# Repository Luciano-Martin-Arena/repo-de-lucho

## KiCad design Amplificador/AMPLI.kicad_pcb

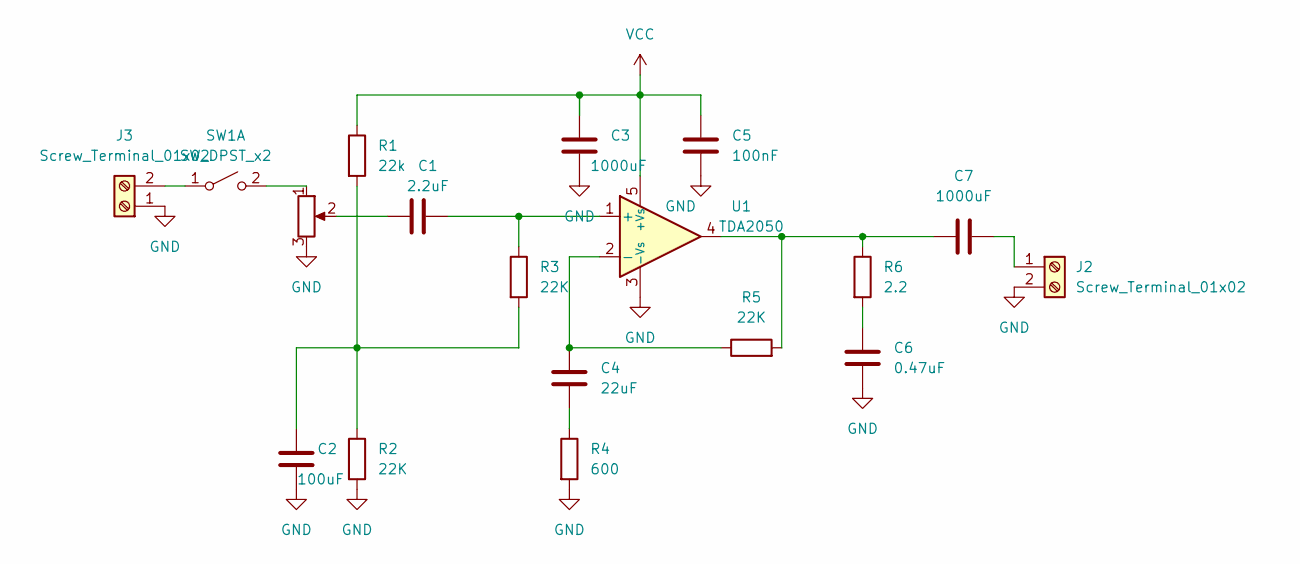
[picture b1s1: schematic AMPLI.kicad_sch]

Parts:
C1: 2.2uF; C_Disc_D3.0mm_W1.6mm_P2.50mm
C2: 100uF; C_Disc_D3.0mm_W1.6mm_P2.50mm
C3, C7: 1000uF; C_Disc_D3.0mm_W1.6mm_P2.50mm
C4: 22uF; C_Disc_D3.0mm_W1.6mm_P2.50mm
C5: 100nF; C_Disc_D3.0mm_W1.6mm_P2.50mm
C6: 0.47uF; C_Disc_D3.0mm_W1.6mm_P2.50mm
J2, J3: Screw_Terminal_01x02; BORNERA2_AZUL
R1: 22k; R_Axial_DIN0204_L3.6mm_D1.6mm_P7.62mm_Horizontal
R2, R3, R5: 22K; R_Axial_DIN0204_L3.6mm_D1.6mm_P7.62mm_Horizontal
R4: 600; R_Axial_DIN0204_L3.6mm_D1.6mm_P7.62mm_Horizontal
R6: 2.2; R_Axial_DIN0204_L3.6mm_D1.6mm_P7.62mm_Horizontal
RV1: R_Potentiometer; Potentiometer_Piher_PC-16_Single_Horizontal
SW1: SW_DPST_x2; PinHeader_1x03_P2.54mm_Vertical
U1: TDA2050; TO-220-5_P3.4x3.7mm_StaggerOdd_Lead3.8mm_Vertical

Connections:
GND: C2.2, C3.2, C5.2, C6.2, J2.2, J3.1, R2.2, R4.2, RV1.3, U1.3 (-Vs)
unnamed: C1.1, RV1.2
unnamed: C2.1, R1.2, R2.1, R3.2
unnamed: C4.2, R4.1
unnamed: C6.1, R6.2
unnamed: C7.1, R5.2, R6.1, U1.4
unnamed: C7.2, J2.1
unnamed: J3.2, SW1.1 (A)
unnamed: RV1.1, SW1.2 (B)
unnamed: C1.2, R3.1, U1.1 (+)
unnamed: C4.1, R5.1, U1.2 (-)
VCC: C3.1, C5.1, R1.1, U1.5 (+Vs)

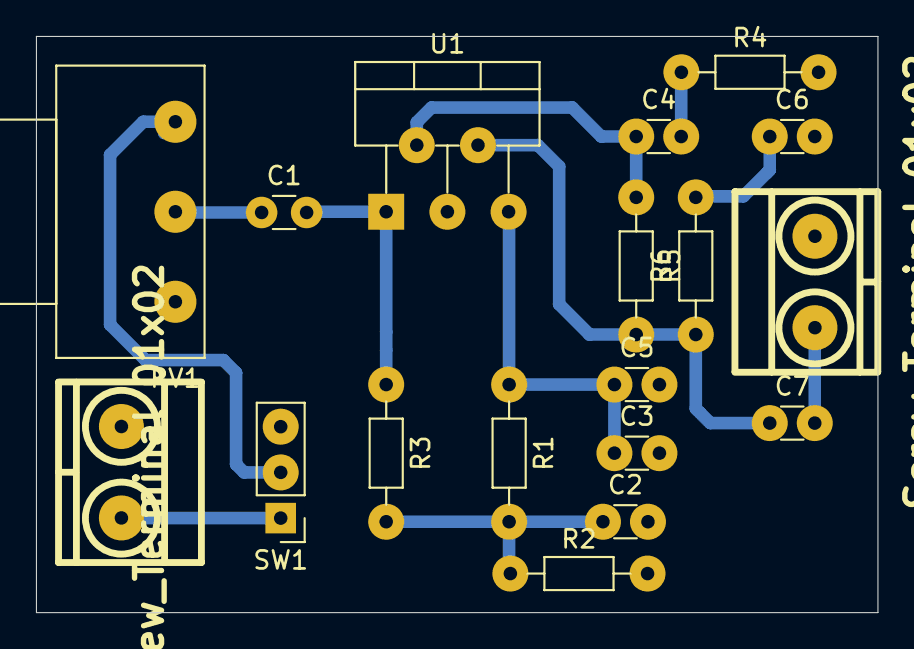
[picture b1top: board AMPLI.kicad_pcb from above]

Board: 2 copper layers, 46.8 x 32.0 mm, 18 parts (0 on the bottom side), 12 nets.

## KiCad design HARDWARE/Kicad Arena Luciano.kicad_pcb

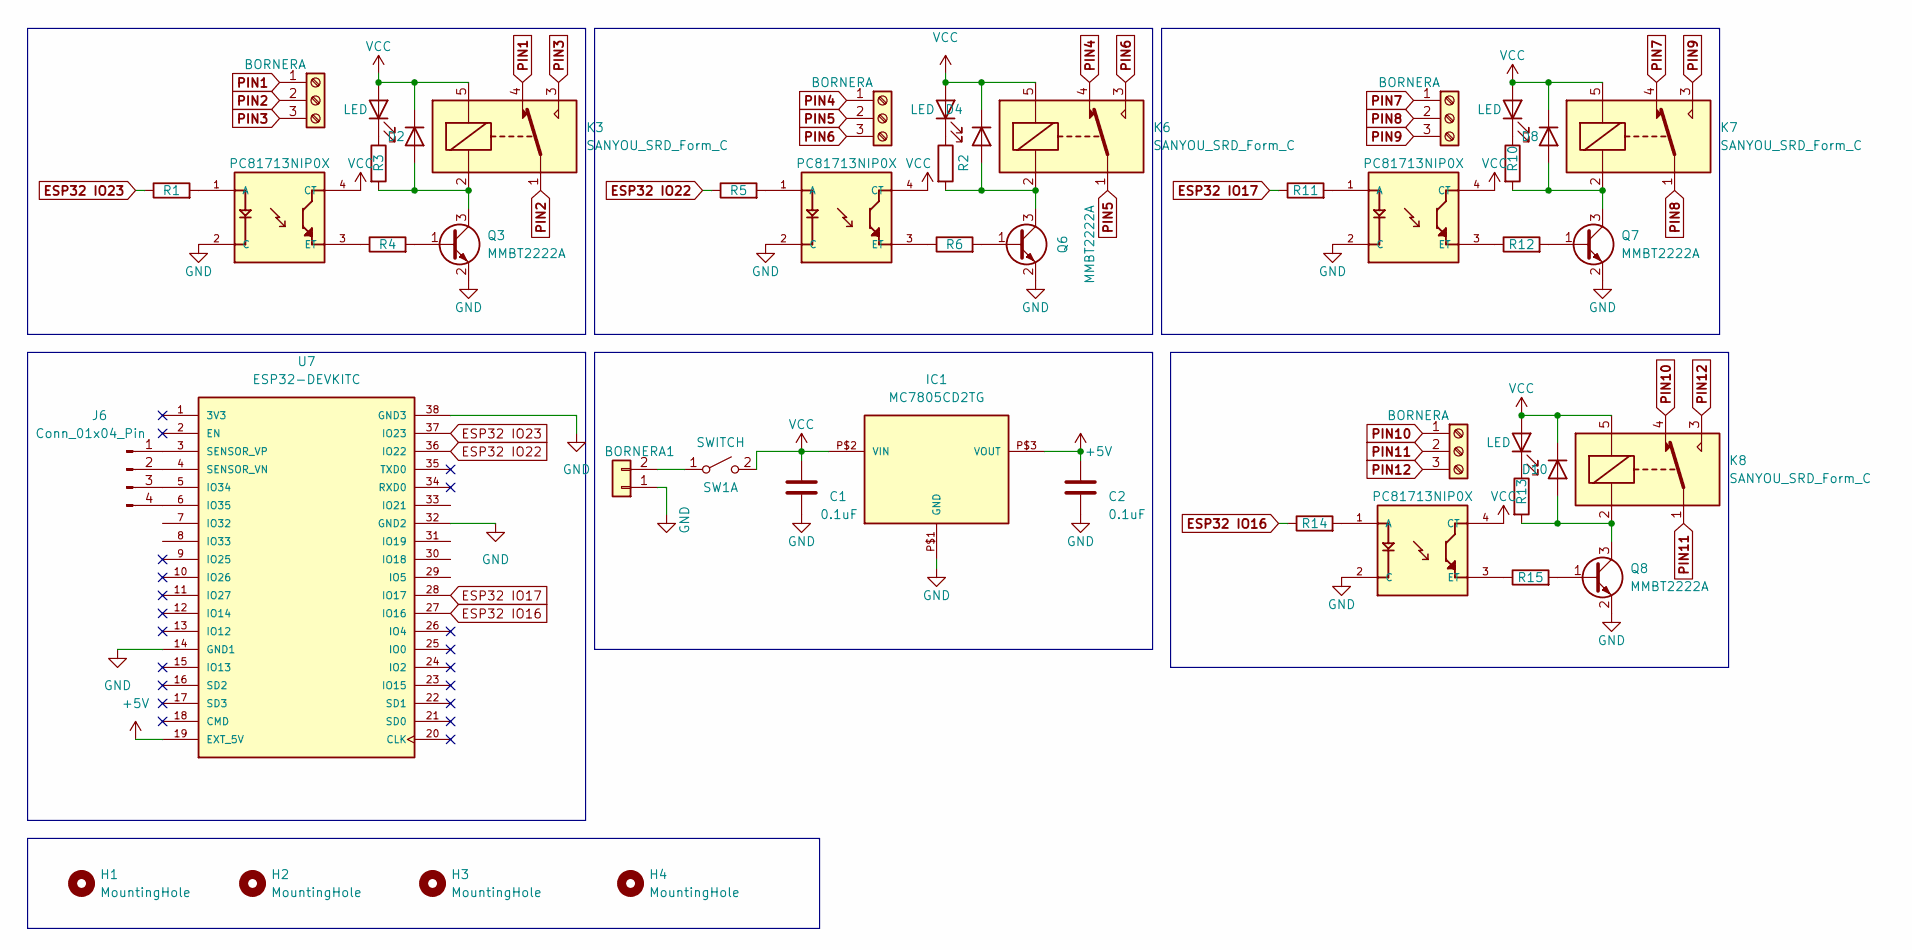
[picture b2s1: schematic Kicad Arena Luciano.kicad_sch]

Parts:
BORNERA1: TerminalBlock_bornier-2_P5.08mm
C1, C2: 0.1uF; C_0805_2012Metric
D1, D3, D7, D9: LED; LED_0805_2012Metric_Pad1.15x1.40mm_HandSolder
D2, D4, D8, D10: D; D_SMA
H1, H2, H3, H4: MountingHole; MountingHole_3.2mm_M3
IC1: MC7805CD2TG
J1, J2, J4, J5: BORNERA; TerminalBlock_bornier-3_P5.08mm
J6: Conn_01x04_Pin; PinHeader_1x04_P2.54mm_Vertical
K3, K6, K7, K8: SANYOU_SRD_Form_C; Relay_SPDT_SANYOU_SRD_Series_Form_C
Q3, Q6, Q7, Q8: MMBT2222A; SOT-23
R1, R2, R3, R4, R5, R6, R10, R11, R12, R13, R14, R15: R; R_0805_2012Metric
SW1: SWITCH; PinHeader_1x02_P2.54mm_Vertical
U1, U2, U4, U5: PC81713NIP0X; SOT254P1025X400-4N
U7: ESP32-DEVKITC; ESP32S; PARTREV N/A

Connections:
ESP32 IO17: R11.1
+5V: C2.1, IC1.P$3 (VOUT), U7.19 (EXT_5V)
ESP32 IO16: R14.1, U7.27 (IO16)
ESP32 IO17: U7.28 (IO17)
ESP32 IO22: R5.1, U7.36 (IO22)
ESP32 IO23: R1.1, U7.37 (IO23)
GND: BORNERA1.1, C1.2, C2.2, IC1.P$1 (GND), Q3.2 (E), Q6.2 (E), Q7.2 (E), Q8.2 (E), U1.2 (C), U2.2 (C), U4.2 (C), U5.2 (C), U7.14 (GND1), U7.32 (GND2), U7.38 (GND3)
unnamed: BORNERA1.2, SW1.1 (A)
unnamed: D1.1 (K), R2.1
unnamed: D2.2 (A), K3.2, Q3.3 (C), R3.2
unnamed: D3.1 (K), R3.1
unnamed: D4.2 (A), K6.2, Q6.3 (C), R2.2
unnamed: D7.1 (K), R10.1
unnamed: D8.2 (A), K7.2, Q7.3 (C), R10.2
unnamed: D9.1 (K), R13.1
unnamed: D10.2 (A), K8.2, Q8.3 (C), R13.2
unnamed: J6.1, U7.3 (SENSOR_VP)
unnamed: J6.2, U7.4 (SENSOR_VN)
unnamed: J6.3, U7.5 (IO34)
unnamed: J6.4, U7.6 (IO35)
unnamed: Q3.1 (B), R4.2
unnamed: Q6.1 (B), R6.2
unnamed: Q7.1 (B), R12.2
unnamed: Q8.1 (B), R15.2
unnamed: R1.2, U1.1 (A)
unnamed: R4.1, U1.3 (ET)
unnamed: R5.2, U2.1 (A)
unnamed: R6.1, U2.3 (ET)
unnamed: R11.2, U4.1 (A)
unnamed: R12.1, U4.3 (ET)
unnamed: R14.2, U5.1 (A)
unnamed: R15.1, U5.3 (ET)
PIN1: J1.1, K3.4
PIN2: J1.2, K3.1
PIN3: J1.3, K3.3
PIN4: J2.1, K6.4
PIN5: J2.2, K6.1
PIN6: J2.3, K6.3
PIN7: J4.1, K7.4
PIN8: J4.2, K7.1
PIN9: J4.3, K7.3
PIN10: J5.1, K8.4
PIN11: J5.2, K8.1
PIN12: J5.3, K8.3
VCC: C1.1, D1.2 (A), D2.1 (K), D3.2 (A), D4.1 (K), D7.2 (A), D8.1 (K), D9.2 (A), D10.1 (K), IC1.P$2 (VIN), K3.5, K6.5, K7.5, K8.5, SW1.2 (B), U1.4 (CT), U2.4 (CT), U4.4 (CT), U5.4 (CT)

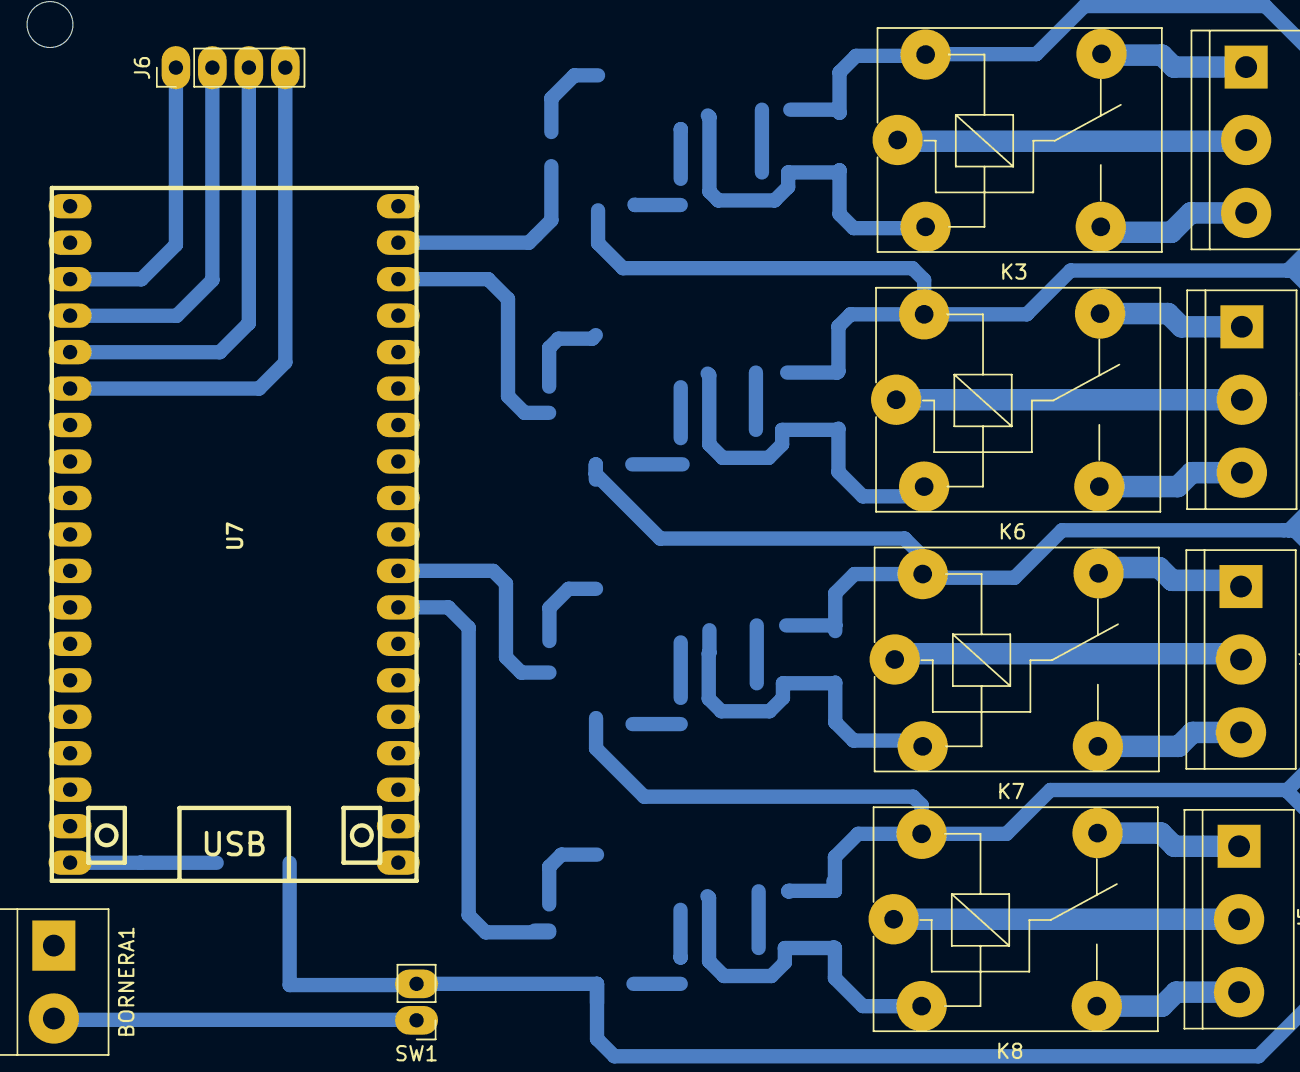
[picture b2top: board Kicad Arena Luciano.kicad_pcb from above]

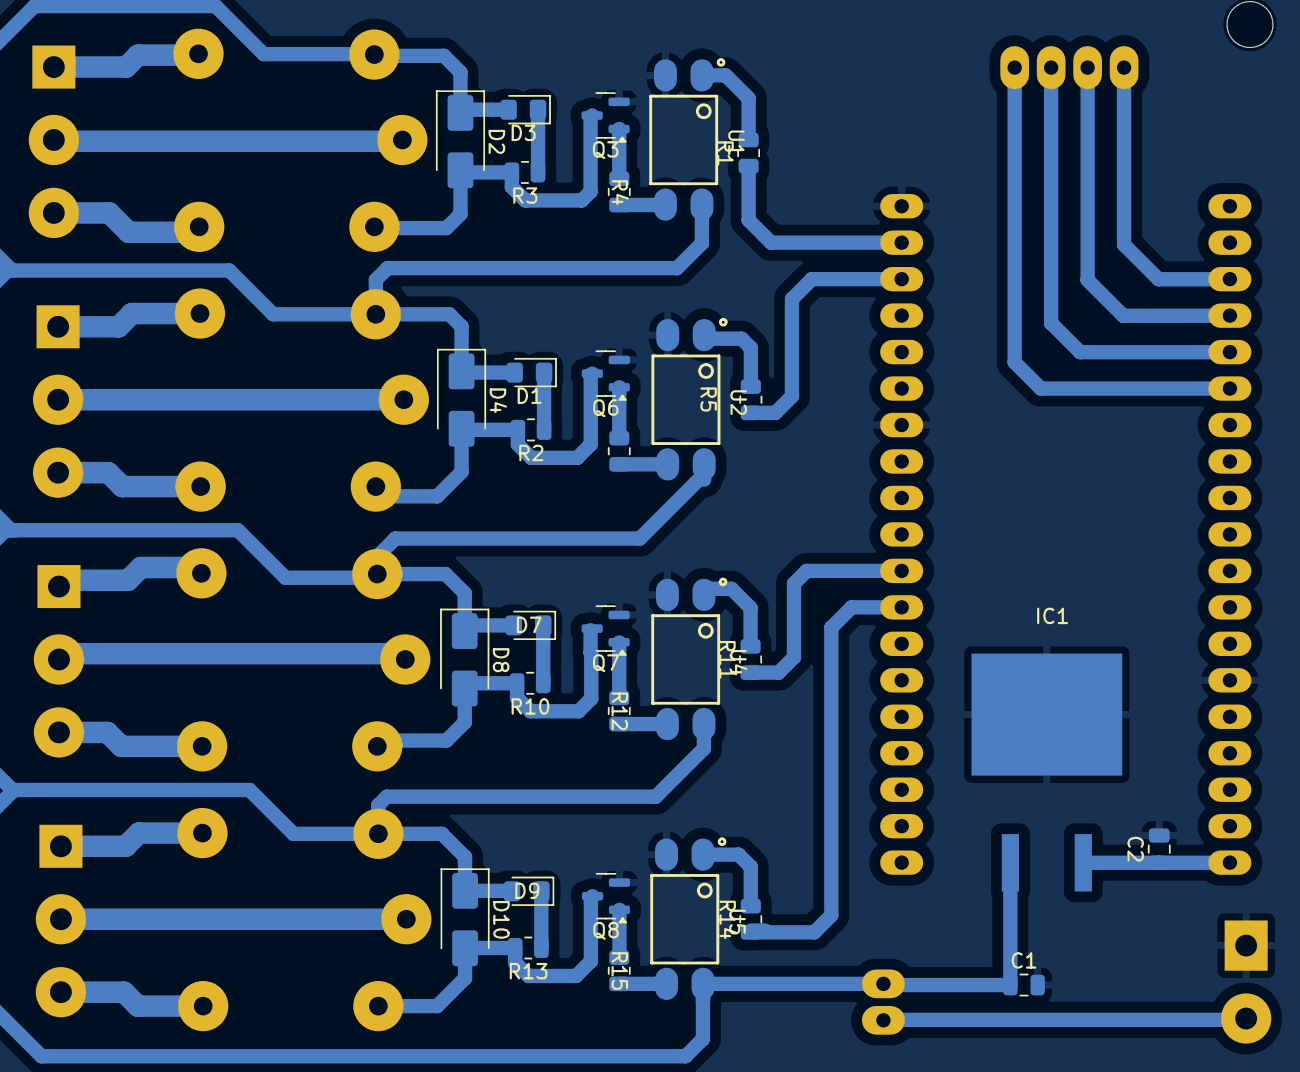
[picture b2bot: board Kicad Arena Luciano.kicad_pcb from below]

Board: 2 copper layers, 47 parts (31 on the bottom side), 43 nets.

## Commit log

2025-04-14 “Miprimercommit”
2025-05-13 Create HADWARE
2025-06-06 nuevo
2025-06-23 comi2
2025-06-25 commit3
2025-06-25 commit4
2025-09-08 commit777
2025-09-17 commit20
2025-09-17 commit22
2025-11-07 commit18
2025-11-07 commit19
